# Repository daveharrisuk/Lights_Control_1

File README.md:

# Lights_Control_1
Arduino Lighting control module for 10 LED strings.

10 PWM channels drive 10 LED strings. 

Input (Day/Night) triggers channel modes...

 DAYNIGHT : Duty cycle (DC) transition on trigger
 DAWN : DC transitions on input changing to day
 DUSK : DC transitions on input changing to night
 DUSKDAWN : DC transitions on input change
 NIGHTONOFF : During night time, LEDs transition at durations

Transition config:
 - Delay seconds before transitions.
 - Transition duration in seconds.

Duty Cycle Day and Night config.

Configurations are defined in seperate CONFIG.h file.
This sketch has 4 configs builtin. Address jumpers select 1 of 4 configs.

Over current protection. Audio alarm sounder.
Serial Monitor provides simple diagnostics. 

This version uses logic signal input (opto isolated) as day/night trigger.

Possible future options...
  SPI bus on PCB to have input trigger via CBUS.
  LCD via I2C bus & rotary encoder for local configuration method.

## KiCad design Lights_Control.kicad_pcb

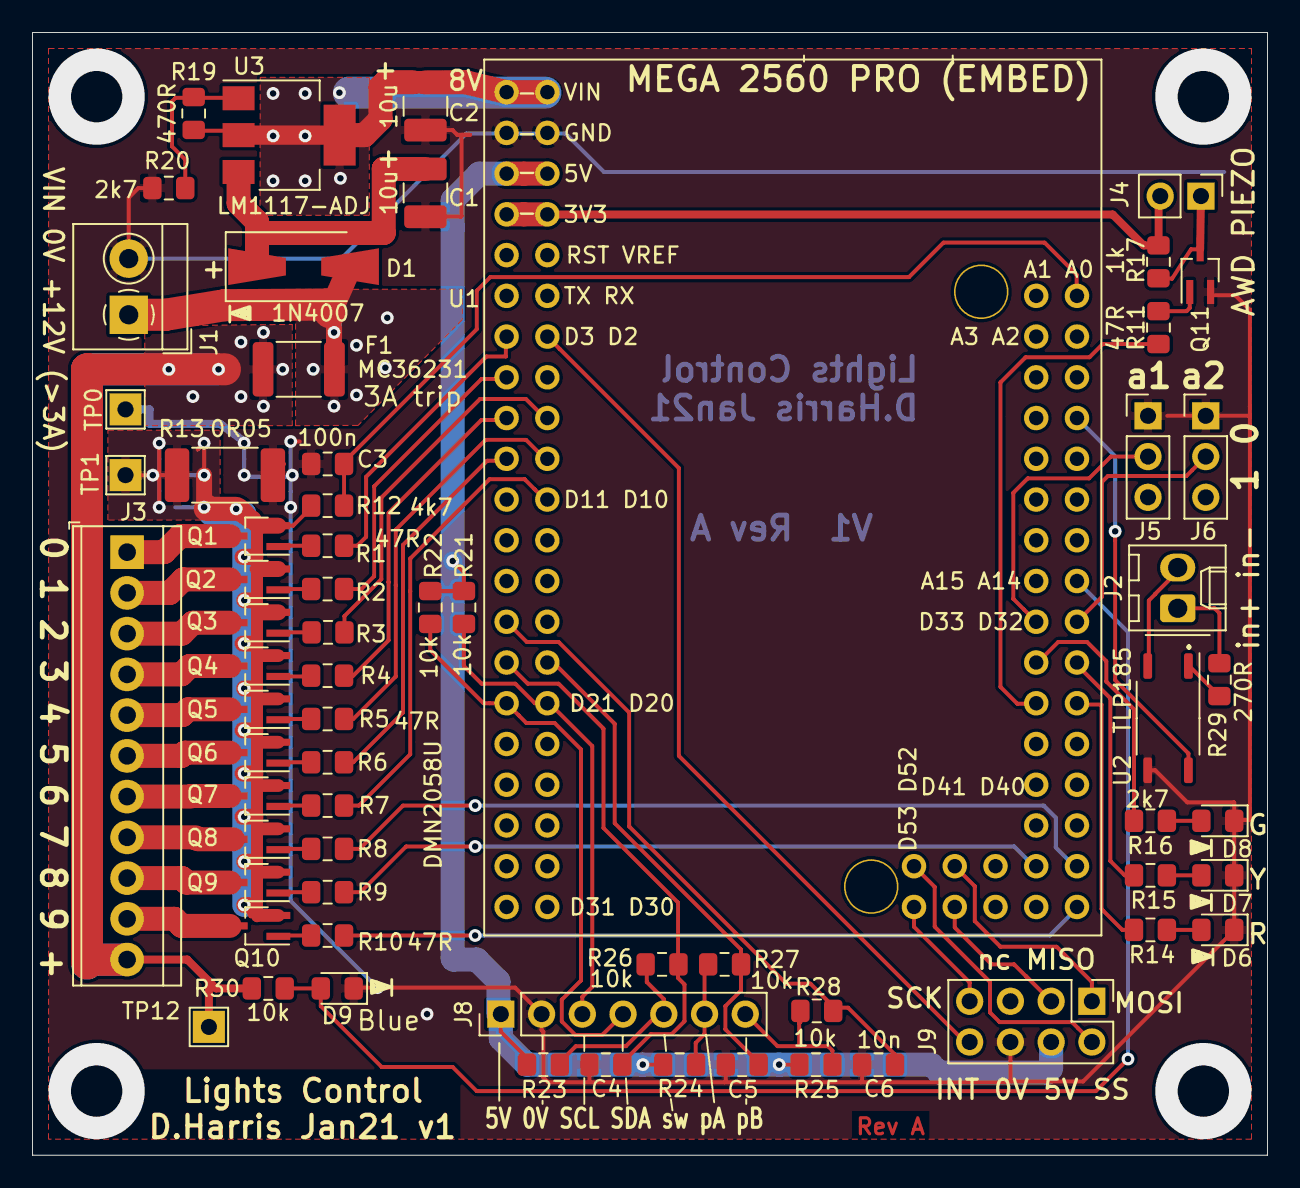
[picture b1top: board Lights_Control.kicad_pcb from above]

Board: 2 copper layers, 77.0 x 70.0 mm, 66 parts (0 on the bottom side), 69 nets.

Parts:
C1, C2: 10u; C_1210_3225Metric_Pad1.42x2.65mm_HandSolder
C3: 100n; C_0805_2012Metric_Pad1.15x1.40mm_HandSolder
C4, C5, C6: 10n; C_0805_2012Metric_Pad1.15x1.40mm_HandSolder
D1: 1N4007; D_SMA-SMB_Universal_Handsoldering
D6: Red; LED_0805_2012Metric_Pad1.15x1.40mm_HandSolder
D7: Yellow; LED_0805_2012Metric_Pad1.15x1.40mm_HandSolder
D8: Green; LED_0805_2012Metric_Pad1.15x1.40mm_HandSolder
D9: Blue; LED_0805_2012Metric_Pad1.15x1.40mm_HandSolder
F1: MC36231; Fuse_1812_4532Metric_Pad1.30x3.40mm_HandSolder
J1: TH 3.5mm 2way Screw; TerminalBlock_4Ucon_1x02_P3.50mm_Horizontal
J2: TH 2.54mm 2way Molex KK; Molex_KK-254_AE-6410-02A_1x02_P2.54mm_Vertical
J3: TH 2.54mm 11way header; TerminalBlock_TE_1-282834-1_1x11_P2.54mm_Horizontal
J4: TH 2.54mm 2way header; PinHeader_1x02_P2.54mm_Vertical
J5: Conn_01x03_Male; PinHeader_1x03_P2.54mm_Vertical
J6: TH 2.54mm 3way header; PinHeader_1x03_P2.54mm_Vertical
J8: TH 2.54 7way socket; PinHeader_1x07_P2.54mm_Vertical
J9: TH 2.54mm 2 row 8 contact header; PinHeader_2x04_P2.54mm_Vertical
Q1, Q2, Q3, Q4, Q5, Q6, Q7, Q8, Q9, Q10, Q11: DMN2058U; SOT-323_SC-70_Handsoldering
R1, R2, R3, R4, R5, R6, R7, R8, R9, R10, R11: 47R; R_0805_2012Metric_Pad1.15x1.40mm_HandSolder
R12: 4k7; R_0805_2012Metric_Pad1.15x1.40mm_HandSolder
R13: 0R05; R_2512_6332Metric_Pad1.52x3.35mm_HandSolder
R14, R15, R16, R20: 2k7; R_0805_2012Metric_Pad1.15x1.40mm_HandSolder
R17: 1k; R_0805_2012Metric_Pad1.15x1.40mm_HandSolder
R19: 470R; R_0805_2012Metric_Pad1.15x1.40mm_HandSolder
R21, R22, R23, R24, R25, R26, R27, R28, R30: 10k; R_0805_2012Metric_Pad1.15x1.40mm_HandSolder
R29: 270R; R_0805_2012Metric_Pad1.15x1.40mm_HandSolder
TP0, TP1, TP12: TestPoint; TestPoint_THTPad_2.0x2.0mm_Drill1.0mm
U1: MEGA_PRO_EMBED_CH340G___ATMEGA2560; MEGA_2560_PRO(EMBED)
U2: TLP185; SOIC-4_4.55x3.7mm_P2.54mm
U3: LM1117-ADJ; SOT-223-3_TabPin2

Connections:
+3V3: J4.2, R17.2, U1.7, U1.8
+5V: J8.1, J9.4, R21.2, R22.2, R23.2, R24.2, R25.2, U1.5, U1.6
+12V: F1.1, J3.11, R30.1, TP12.1
/8V: C2.1, R19.2, U1.1, U1.2, U3.2
/12V: D1.2, F1.2, J1.1
/AWD: J4.1, Q11.3, R17.1
/AWDsig: R11.1, U1.59
/Adr1: J5.2, U1.63
/Adr2: J6.2, U1.64
/In+: J2.1, R29.1
/In-: J2.2, U2.3
/Input: U1.74, U2.6
/LED0: J3.1, Q1.3
/LED1: J3.2, Q2.3
/LED2: J3.3, Q3.3
/LED3: J3.4, Q4.3
/LED4: J3.5, Q5.3
/LED5: J3.6, Q6.3
/LED6: J3.7, Q7.3
/LED7: J3.8, Q8.3
/LED8: J3.9, Q9.3
/LED9: J3.10, Q10.3
/LEDgrn: R16.1, U1.61
/LEDred: R14.1, U1.60
/LEDyel: R15.1, U1.62
/Opto: R29.2, U2.1
/PHA: C5.1, R27.2, U1.30
/PHB: C6.1, R28.2, U1.27
/PWM0: R1.1, U1.13
/PWM1: R2.1, U1.15
/PWM2: R3.1, U1.18
/PWM3: R4.1, U1.17
/PWM4: R5.1, U1.20
/PWM5: R6.1, U1.19
/PWM6: R7.1, U1.22
/PWM7: R8.1, U1.52
/PWM8: R9.1, U1.51
/PWM9: R10.1, U1.47
/Q1g: Q1.1, R1.2
/Q2g: Q2.1, R2.2
/Q3g: Q3.1, R3.2
/Q4g: Q4.1, R4.2
/Q5g: Q5.1, R5.2
/Q6g: Q6.1, R6.2
/Q7g: Q7.1, R7.2
/Q8g: Q8.1, R8.2
/Q9g: Q9.1, R9.2
/Q10g: Q10.1, R10.2
/Q11g: Q11.1, R11.2
/SCL: J8.3, R21.1, U1.32
/SDA: J8.4, R22.1, U1.31
/SPI_INT: J9.8, U1.14
/SPI_MISO: J9.3, U1.44
/SPI_MOSI: J9.1, U1.49
/SPI_SCK: J9.7, U1.43
/SPI_SS: J9.2, U1.48
/SW: C4.1, R26.2, U1.29
/Sense: C3.1, R12.1, U1.80
/blue: D9.2, R30.2, U1.66
/grn: D8.2, R16.2
/pha-: J8.6, R24.1, R27.1
/phb-: J8.7, R25.1, R28.1
/red: D6.2, R14.2
/senseR: Q1.2, Q2.2, Q3.2, Q4.2, Q5.2, Q6.2, Q7.2, Q8.2, Q9.2, Q10.2, R12.2, R13.1, TP1.1
/sw-: J8.5, R23.1, R26.1
/yel: D7.2, R15.2
GND: C1.2, C2.2, C3.2, C4.2, C5.2, C6.2, D6.1, D7.1, D8.1, D9.1, J1.2, J5.1, J6.1, J8.2, J9.6, Q11.2, R13.2, R20.1, TP0.1, U1.3, U1.4, U2.4
unnamed: C1.1, D1.1, U3.3
unnamed: R19.1, R20.2, U3.1
